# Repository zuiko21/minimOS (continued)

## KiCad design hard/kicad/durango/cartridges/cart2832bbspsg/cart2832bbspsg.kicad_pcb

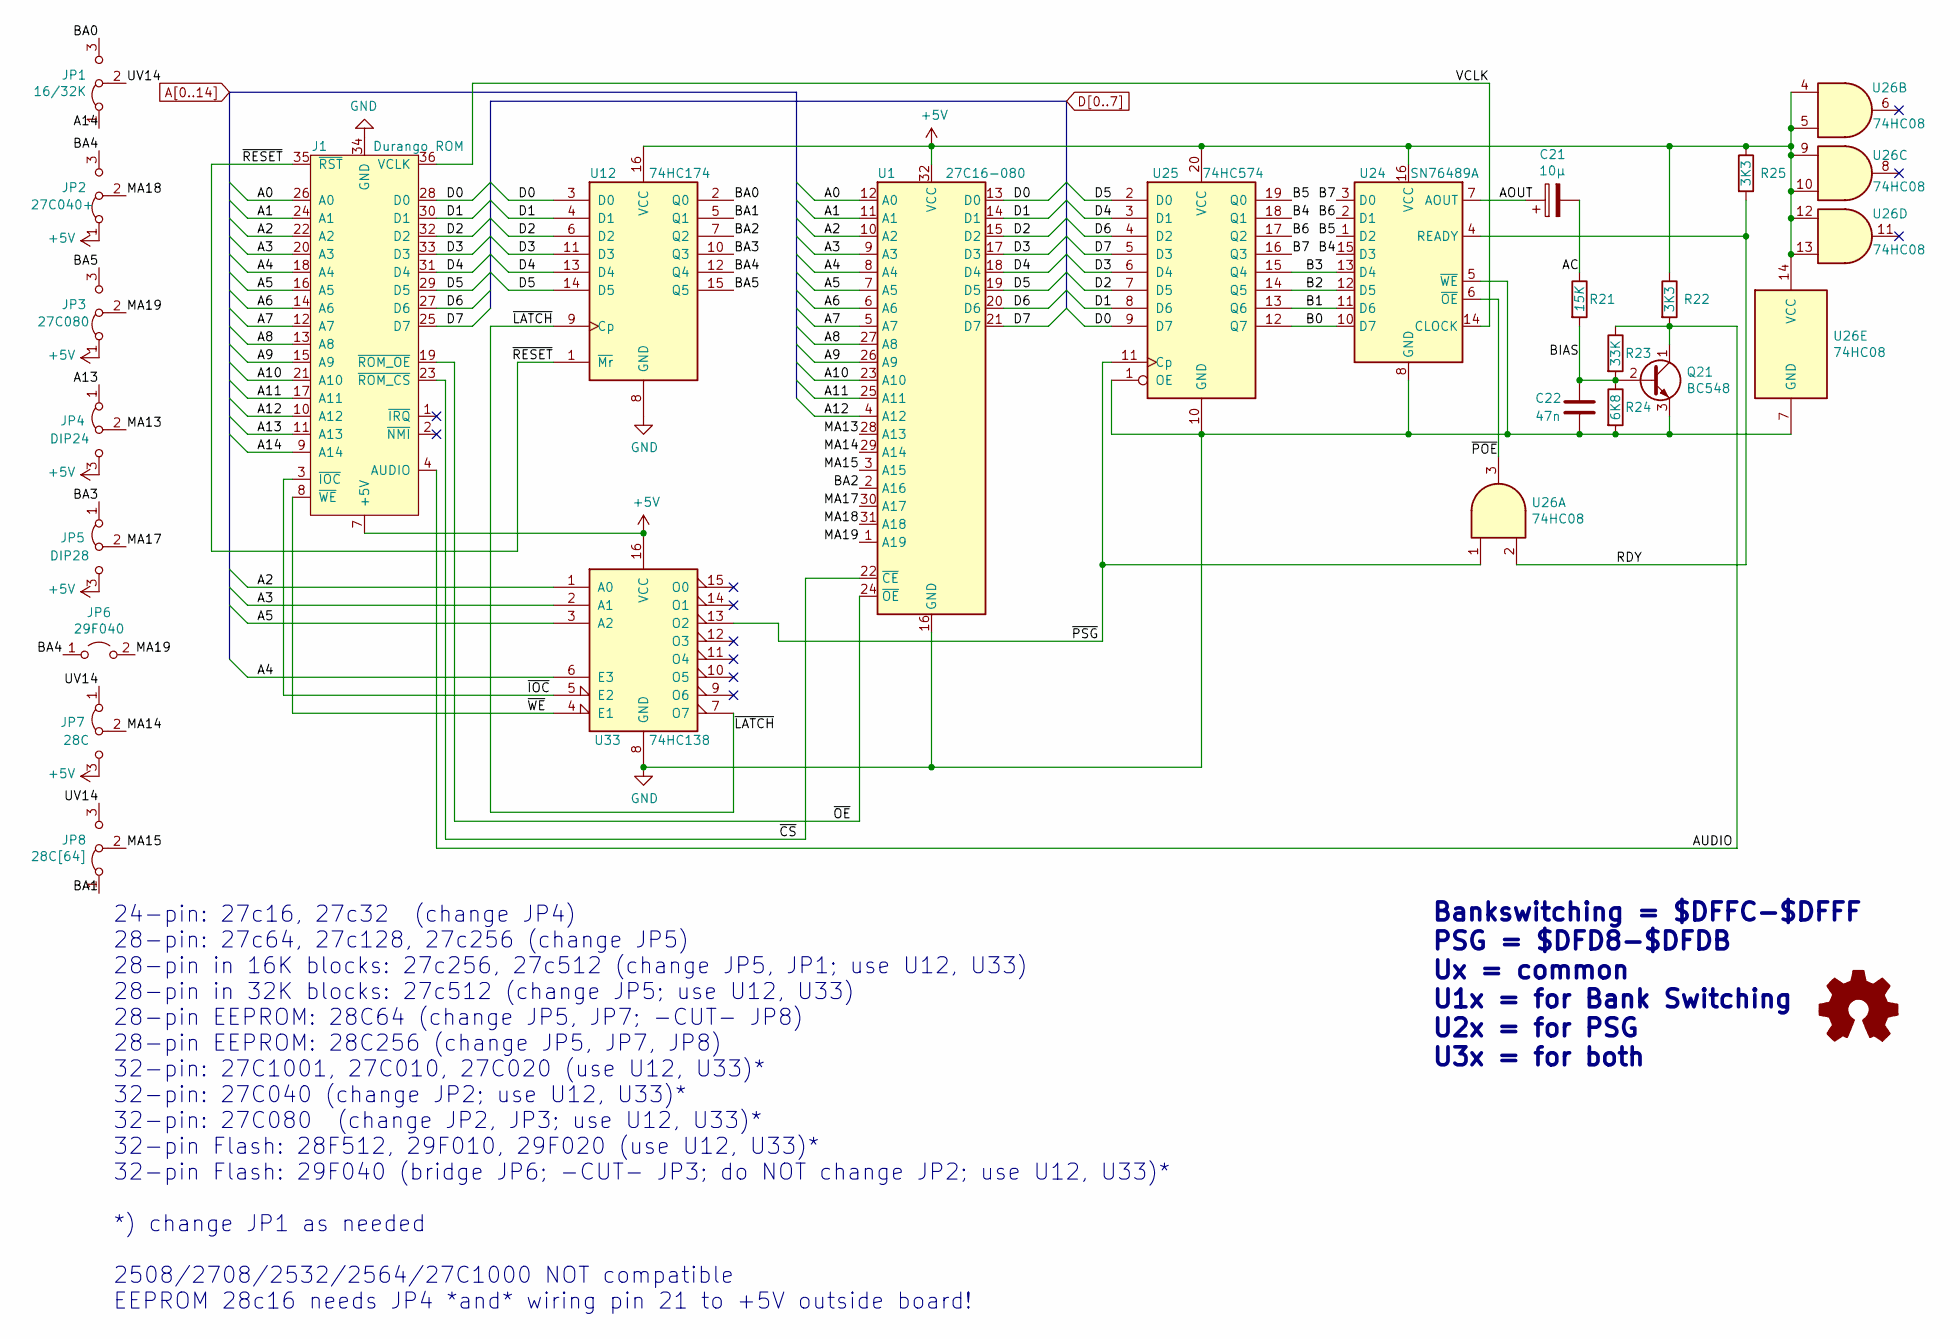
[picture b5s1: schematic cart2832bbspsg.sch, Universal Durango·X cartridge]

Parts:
C21: 10µ; CP_Radial_D4.0mm_P1.50mm
C22: 47n; C_Disc_D3.8mm_W2.6mm_P2.50mm
J1: Durango ROM; Durango_ROM
JP1: 16/32K; SolderJumper-3_P1.3mm_Bridged12_RoundedPad1.0x1.5mm
JP2: 27C040+; SolderJumper-3_P1.3mm_Bridged12_RoundedPad1.0x1.5mm
JP3: 27C080; SolderJumper-3_P1.3mm_Bridged12_RoundedPad1.0x1.5mm
JP4: DIP24; SolderJumper-3_P1.3mm_Bridged12_RoundedPad1.0x1.5mm
JP5: DIP28; SolderJumper-3_P1.3mm_Bridged12_RoundedPad1.0x1.5mm
JP6: 29F040; SolderJumper-2_P1.3mm_Open_RoundedPad1.0x1.5mm
JP7: 28C; SolderJumper-3_P1.3mm_Bridged12_RoundedPad1.0x1.5mm
JP8: 28C[64]; SolderJumper-3_P1.3mm_Bridged12_RoundedPad1.0x1.5mm
LOGO1: Logo_Open_Hardware_Small; jaqueria
Q21: BC548; TO-92_Inline
R21: 15K; R_Axial_DIN0207_L6.3mm_D2.5mm_P10.16mm_Horizontal
R22, R25: 3K3; R_Axial_DIN0207_L6.3mm_D2.5mm_P10.16mm_Horizontal
R23: 33K; R_Axial_DIN0207_L6.3mm_D2.5mm_P10.16mm_Horizontal
R24: 6K8; R_Axial_DIN0207_L6.3mm_D2.5mm_P10.16mm_Horizontal
U1: 27C16-080; DIP-32_W15.24mm
U12: 74HC174; DIP-16_W7.62mm
U24: SN76489A; DIP-16_W7.62mm
U25: 74HC574; DIP-20_W7.62mm
U26: 74HC08; DIP-14_W7.62mm
U33: 74HC138; DIP-16_W7.62mm

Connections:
+5V: J1.7 (+5V), JP2.1 (A), JP3.1 (A), JP4.3 (B), JP5.3 (B), JP7.3 (B), R22.1, R25.1, U1.32 (VCC), U12.16 (VCC), U24.16 (VCC), U25.20 (VCC), U26.4, U26.5, U26.9, U26.10, U26.12, U26.13, U26.14 (VCC), U33.16 (VCC)
/AC: C21.2, R21.1
/AOUT: C21.1, U24.7 (AOUT)
/AUDIO: J1.4 (AUDIO), Q21.1 (C), R22.2, R23.1
/B0: U24.10 (D7), U25.12 (Q7)
/B1: U24.11 (D6), U25.13 (Q6)
/B2: U24.12 (D5), U25.14 (Q5)
/B3: U24.13 (D4), U25.15 (Q4)
/B4: U24.15 (D3), U25.18 (Q1)
/B5: U24.1 (D2), U25.19 (Q0)
/B6: U24.2 (D1), U25.17 (Q2)
/B7: U24.3 (D0), U25.16 (Q3)
/BA0: JP1.3 (B), U12.2 (Q0)
/BA1: JP8.1 (A), U12.5 (Q1)
/BA2: U1.2 (A16), U12.7 (Q2)
/BA3: JP5.1 (A), U12.10 (Q3)
/BA4: JP2.3 (B), JP6.1 (A), U12.12 (Q4)
/BA5: JP3.3 (B), U12.15 (Q5)
/BIAS: C22.1, Q21.2 (B), R21.2, R23.2, R24.1
/MA13: JP4.2 (C), U1.28 (A13)
/MA14: JP7.2 (C), U1.29 (A14)
/MA15: JP8.2 (C), U1.3 (A15)
/MA17: JP5.2 (C), U1.30 (A17)
/MA18: JP2.2 (C), U1.31 (A18)
/MA19: JP3.2 (C), JP6.2 (B), U1.1 (A19)
/RDY: R25.2, U24.4 (READY), U26.2
/UV14: JP1.2 (C), JP7.1 (A), JP8.3 (B)
/VCLK: J1.36 (VCLK), U24.14 (CLOCK)
/~CS: J1.23 (~ROM_CS), U1.22 (~CE)
/~IOC: J1.3 (~IOC), U33.5 (E2)
/~LATCH: U12.9 (Cp), U33.7 (O7)
/~OE: J1.19 (~ROM_OE), U1.24 (~OE)
/~POE: U24.6 (~OE), U26.3
/~PSG: U25.11 (Cp), U26.1, U33.13 (O2)
/~RESET: J1.35 (~RST), U12.1 (~Mr)
/~WE: J1.8 (~WE), U33.4 (E1)
A0: J1.26 (A0), U1.12 (A0)
A1: J1.24 (A1), U1.11 (A1)
A2: J1.22 (A2), U1.10 (A2), U33.1 (A0)
A3: J1.20 (A3), U1.9 (A3), U33.2 (A1)
A4: J1.18 (A4), U1.8 (A4), U33.6 (E3)
A5: J1.16 (A5), U1.7 (A5), U33.3 (A2)
A6: J1.14 (A6), U1.6 (A6)
A7: J1.12 (A7), U1.5 (A7)
A8: J1.13 (A8), U1.27 (A8)
A9: J1.15 (A9), U1.26 (A9)
A10: J1.21 (A10), U1.23 (A10)
A11: J1.17 (A11), U1.25 (A11)
A12: J1.10 (A12), U1.4 (A12)
A13: J1.11 (A13), JP4.1 (A)
A14: J1.9 (A14), JP1.1 (A)
D0: J1.28 (D0), U1.13 (D0), U12.3 (D0), U25.9 (D7)
D1: J1.30 (D1), U1.14 (D1), U12.4 (D1), U25.8 (D6)
D2: J1.32 (D2), U1.15 (D2), U12.6 (D2), U25.7 (D5)
D3: J1.33 (D3), U1.17 (D3), U12.11 (D3), U25.6 (D4)
D4: J1.31 (D4), U1.18 (D4), U12.13 (D4), U25.3 (D1)
D5: J1.29 (D5), U1.19 (D5), U12.14 (D5), U25.2 (D0)
D6: J1.27 (D6), U1.20 (D6), U25.4 (D2)
D7: J1.25 (D7), U1.21 (D7), U25.5 (D3)
GND: C22.2, J1.34 (GND), Q21.3 (E), R24.2, U1.16 (GND), U12.8 (GND), U24.5 (~WE), U24.8 (GND), U25.1 (OE), U25.10 (GND), U26.7 (GND), U33.8 (GND)

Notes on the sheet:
Bankswitching = $DFFC-$DFFF PSG = $DFD8-$DFDB Ux = common U1x = for Bank Switching U2x = for PSG U3x = for both
24-pin: 27c16, 27c32 (change JP4) 28-pin: 27c64, 27c128, 27c256 (change JP5) 28-pin in 16K blocks: 27c256, 27c512 (change JP5, JP1; use U12, U33) 28-pin in 32K blocks: 27c512 (change JP5; use U12, U33) 28-pin EEPROM: 28C64 (change JP5, JP7; -CUT- JP8) 28-pin EEPROM: 28C256 (change JP5, JP7, JP8) 32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

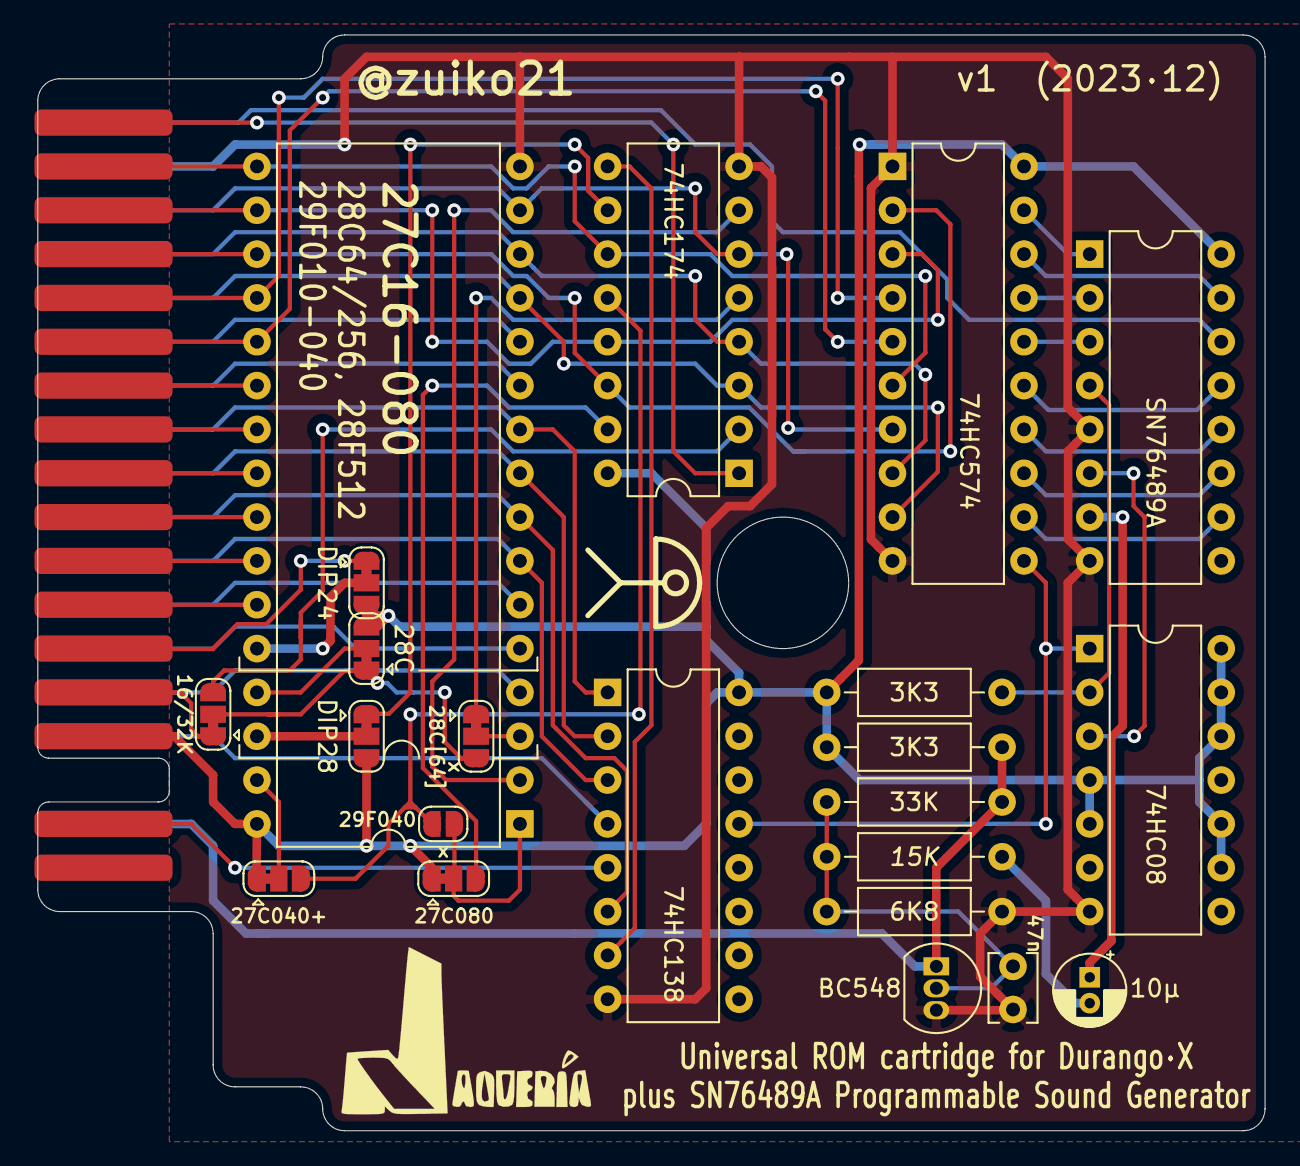
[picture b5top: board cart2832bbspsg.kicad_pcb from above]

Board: 2 copper layers, 71.1 x 63.5 mm, 24 parts (0 on the bottom side), 60 nets.

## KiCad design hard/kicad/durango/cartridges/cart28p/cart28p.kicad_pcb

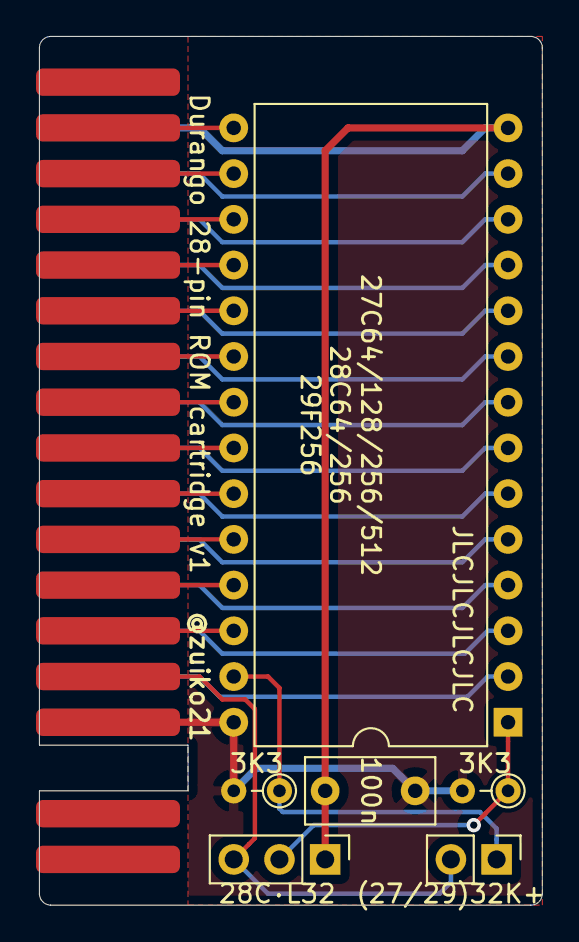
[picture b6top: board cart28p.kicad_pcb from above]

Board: 2 copper layers, 27.9 x 48.3 mm, 7 parts (0 on the bottom side), 29 nets.

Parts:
C1: 100n; C_Rect_L7.0mm_W3.5mm_P5.00mm
J1: Edge Connector; Durango_ROM
JP1: (27/29)32K+; PinHeader_1x02_P2.54mm_Vertical
JP2: 28C·L32; PinHeader_1x03_P2.54mm_Vertical
R1, R2: 3K3; R_Axial_DIN0204_L3.6mm_D1.6mm_P2.54mm_Vertical
U1: 27C64/128/256/512; DIP-28_W15.24mm

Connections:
+5V: C1.2, J1.7, R1.2, R2.2, U1.28
/A0: J1.26, U1.10
/A1: J1.24, U1.9
/A2: J1.22, U1.8
/A3: J1.20, U1.7
/A4: J1.18, U1.6
/A5: J1.16, U1.5
/A6: J1.14, U1.4
/A7: J1.12, U1.3
/A8: J1.13, U1.25
/A9: J1.15, U1.24
/A10: J1.21, U1.21
/A11: J1.17, U1.23
/A12: J1.10, U1.2
/A13: J1.11, U1.26
/A14: JP1.1, R1.1, U1.27
/A15: JP2.2, R2.1, U1.1
/CA14: J1.9, JP1.2, JP2.3
/D0: J1.28, U1.11
/D1: J1.30, U1.12
/D2: J1.32, U1.13
/D3: J1.33, U1.15
/D4: J1.31, U1.16
/D5: J1.29, U1.17
/D6: J1.27, U1.18
/D7: J1.25, U1.19
/~CS: J1.23, U1.20
/~OE: J1.19, U1.22
GND: C1.1, J1.34, JP2.1, U1.14

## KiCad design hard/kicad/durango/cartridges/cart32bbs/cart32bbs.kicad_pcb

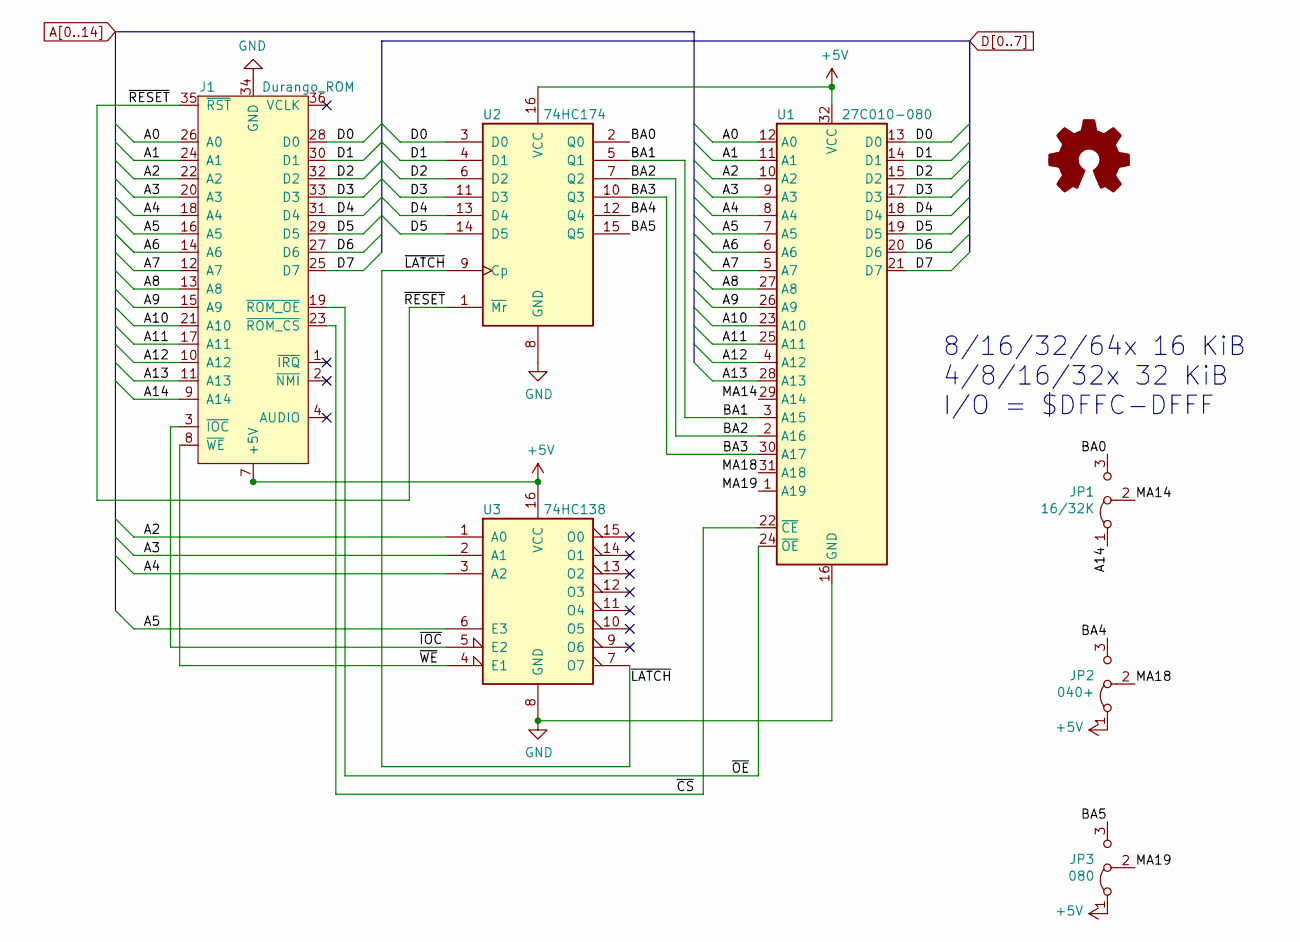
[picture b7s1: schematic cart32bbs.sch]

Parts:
J1: Durango_ROM
JP1: 16/32K; SolderJumper-3_P1.3mm_Bridged12_RoundedPad1.0x1.5mm
JP2: 040+; SolderJumper-3_P1.3mm_Bridged12_RoundedPad1.0x1.5mm
JP3: 080; SolderJumper-3_P1.3mm_Bridged12_RoundedPad1.0x1.5mm
LOGO1: Logo_Open_Hardware_Small; jaqueria
U1: 27C010-080; DIP-32_W15.24mm
U2: 74HC174; DIP-16_W7.62mm
U3: 74HC138; DIP-16_W7.62mm

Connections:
+5V: J1.7 (+5V), JP2.1 (A), JP3.1 (A), U1.32 (VCC), U2.16 (VCC), U3.16 (VCC)
/BA0: JP1.3 (B), U2.2 (Q0)
/BA1: U1.3 (A15), U2.5 (Q1)
/BA2: U1.2 (A16), U2.7 (Q2)
/BA3: U1.30 (A17), U2.10 (Q3)
/BA4: JP2.3 (B), U2.12 (Q4)
/BA5: JP3.3 (B), U2.15 (Q5)
/MA14: JP1.2 (C), U1.29 (A14)
/MA18: JP2.2 (C), U1.31 (A18)
/MA19: JP3.2 (C), U1.1 (A19)
/~CS: J1.23 (~ROM_CS), U1.22 (~CE)
/~IOC: J1.3 (~IOC), U3.5 (E2)
/~LATCH: U2.9 (Cp), U3.7 (O7)
/~OE: J1.19 (~ROM_OE), U1.24 (~OE)
/~RESET: J1.35 (~RST), U2.1 (~Mr)
/~WE: J1.8 (~WE), U3.4 (E1)
A0: J1.26 (A0), U1.12 (A0)
A1: J1.24 (A1), U1.11 (A1)
A2: J1.22 (A2), U1.10 (A2), U3.1 (A0)
A3: J1.20 (A3), U1.9 (A3), U3.2 (A1)
A4: J1.18 (A4), U1.8 (A4), U3.3 (A2)
A5: J1.16 (A5), U1.7 (A5), U3.6 (E3)
A6: J1.14 (A6), U1.6 (A6)
A7: J1.12 (A7), U1.5 (A7)
A8: J1.13 (A8), U1.27 (A8)
A9: J1.15 (A9), U1.26 (A9)
A10: J1.21 (A10), U1.23 (A10)
A11: J1.17 (A11), U1.25 (A11)
A12: J1.10 (A12), U1.4 (A12)
A13: J1.11 (A13), U1.28 (A13)
A14: J1.9 (A14), JP1.1 (A)
D0: J1.28 (D0), U1.13 (D0), U2.3 (D0)
D1: J1.30 (D1), U1.14 (D1), U2.4 (D1)
D2: J1.32 (D2), U1.15 (D2), U2.6 (D2)
D3: J1.33 (D3), U1.17 (D3), U2.11 (D3)
D4: J1.31 (D4), U1.18 (D4), U2.13 (D4)
D5: J1.29 (D5), U1.19 (D5), U2.14 (D5)
D6: J1.27 (D6), U1.20 (D6)
D7: J1.25 (D7), U1.21 (D7)
GND: J1.34 (GND), U1.16 (GND), U2.8 (GND), U3.8 (GND)

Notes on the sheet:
8/16/32/64x 16 KiB 4/8/16/32x 32 KiB I/O = $DFFC-DFFF

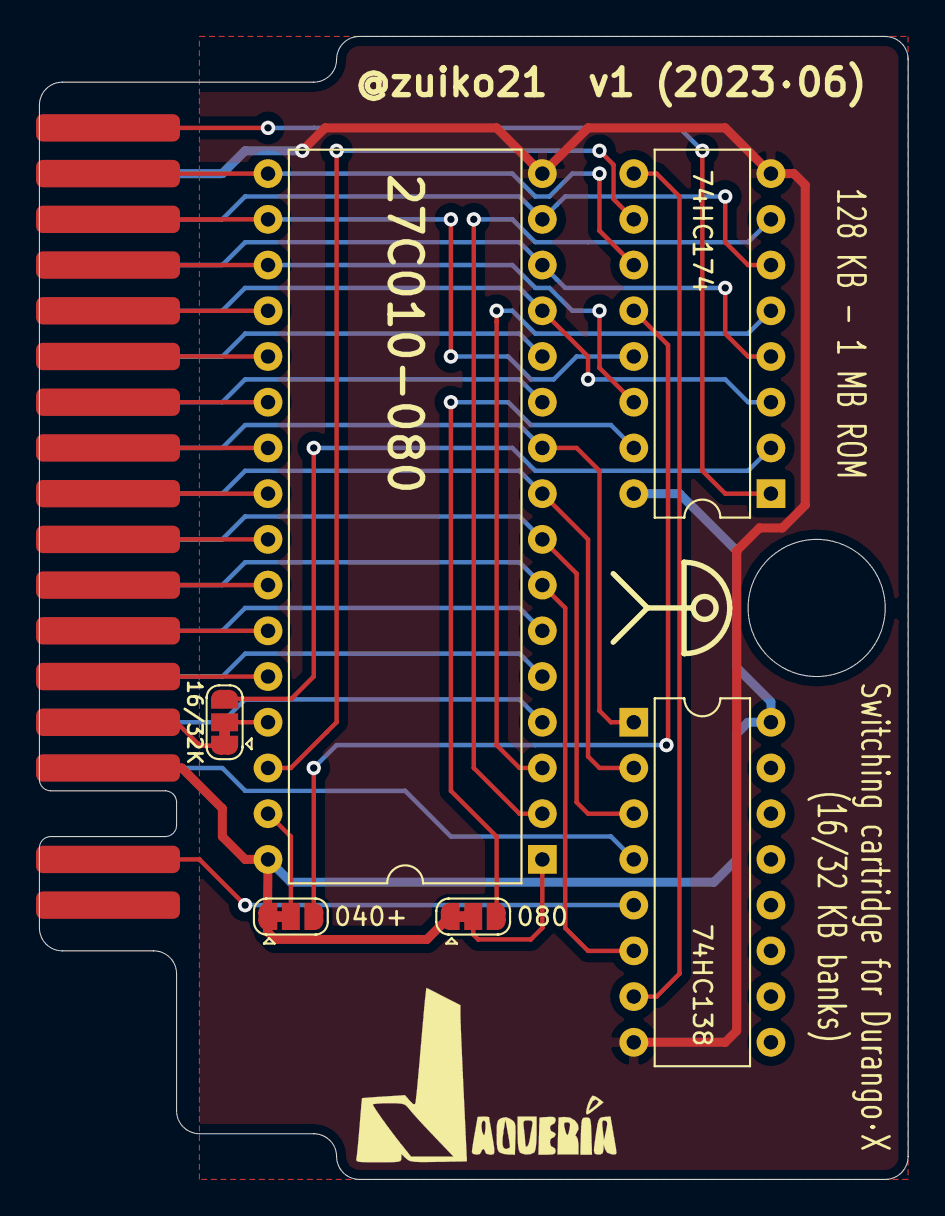
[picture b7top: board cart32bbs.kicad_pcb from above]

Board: 2 copper layers, 48.3 x 63.5 mm, 8 parts (0 on the bottom side), 40 nets.
